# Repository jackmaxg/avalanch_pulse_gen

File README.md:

# avalanch_pulse_gen
Another Incarnation of Jim Williams’ avalanche pulse generator

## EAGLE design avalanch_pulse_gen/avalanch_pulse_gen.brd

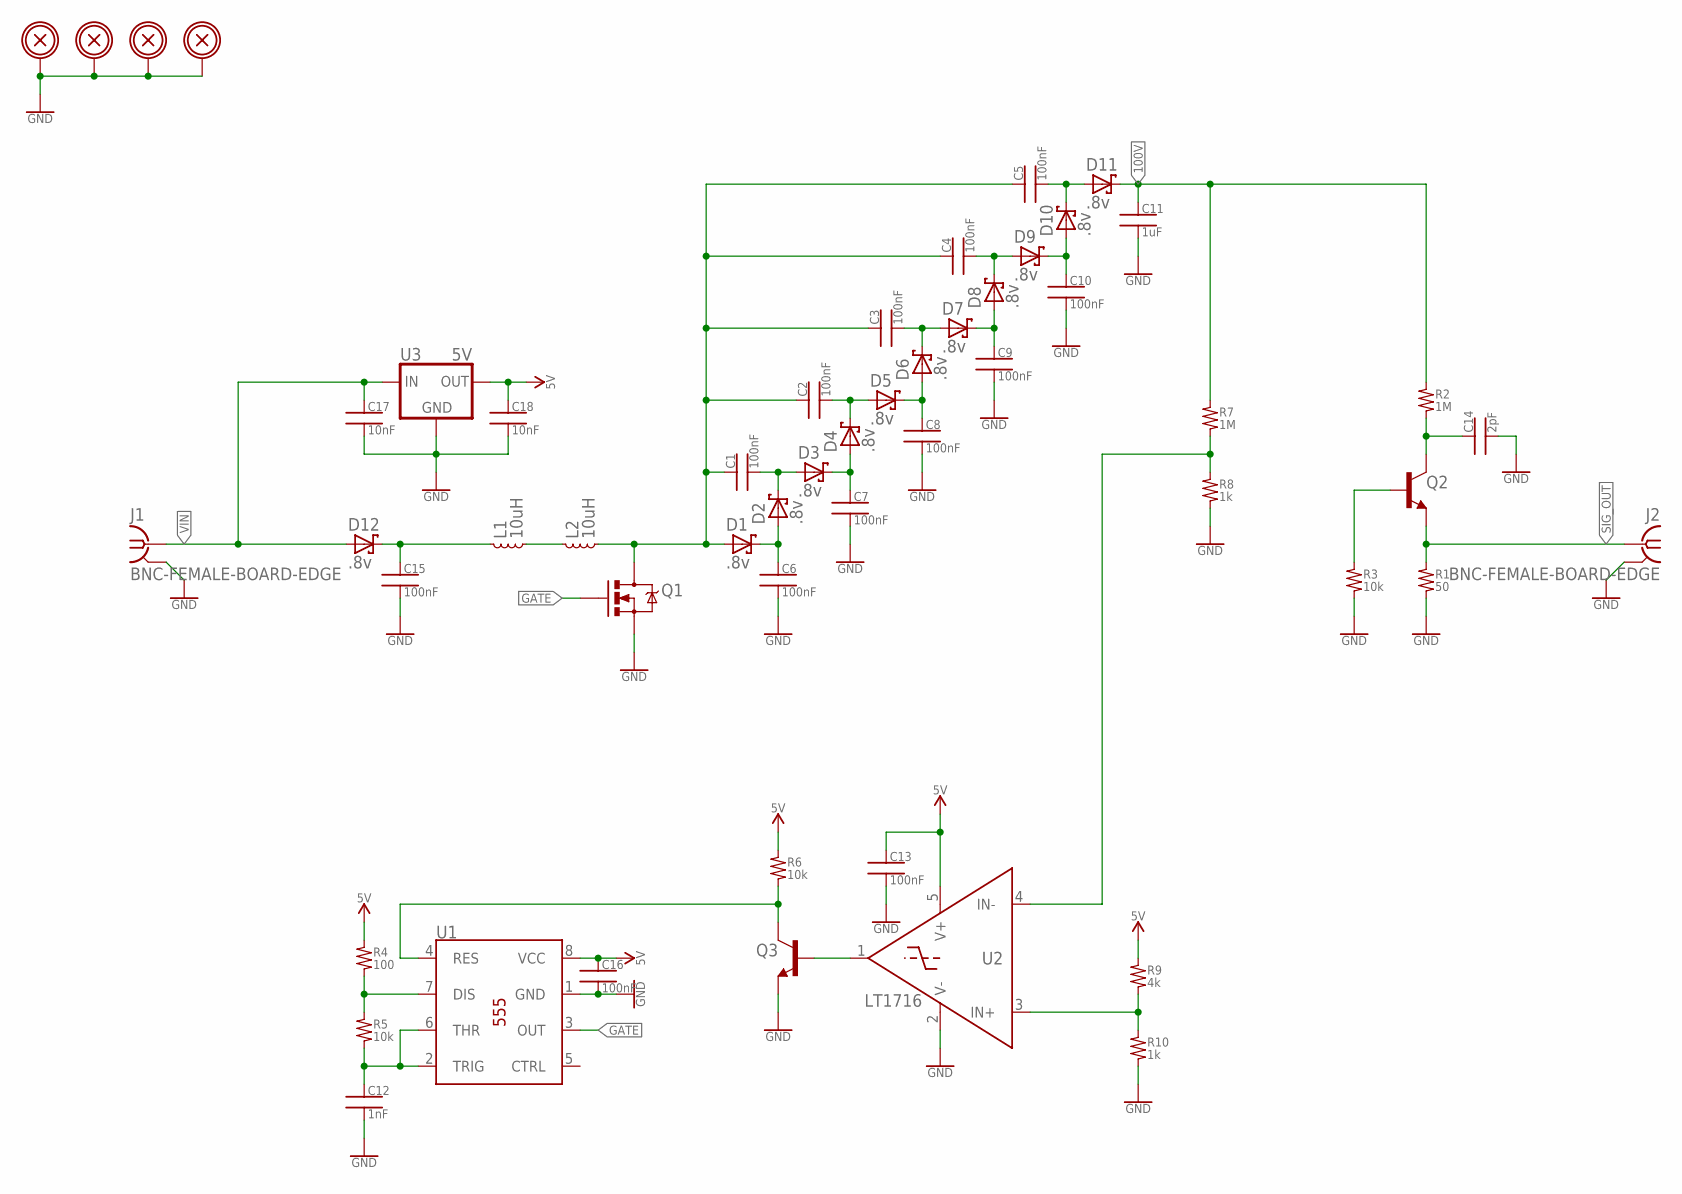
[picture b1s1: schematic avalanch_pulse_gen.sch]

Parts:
C1, C2, C3, C4, C5, C6, C7, C8, C9, C10, C15: 100nF; 1206
C11: 1uF; 2220
C12: 1nF; 0402
C13, C16: 100nF; 0402
C14: 2pF; 0805
C17, C18: 10nF; 0402
D1, D2, D3, D4, D5, D6, D7, D8, D9, D10, D11, D12: .8v; SOD-123
H1, H2, H3, H4: BOLTHOLE_M2.5; M2.5_HOLE
J1, J2: BNC-FEMALE-BOARD-EDGE; AMPHENOL_112640
L1, L2: 10uH; WE74405031100
Q1: MOSFET_N-CHANNEL_SOT23-3; SOT23-3
Q2, Q3: BJT_NPN; SOT23-3
R1: 50; 0402
R2, R7: 1M; 1206
R3, R5, R6: 10k; 0402
R4: 100; 0402
R8, R10: 1k; 0402
R9: 4k; 0402
U1: 555_TIMER_SOIC-8; SOIC_8
U2: LT1716; SOT23-5
U3: 5V; SOT233-4

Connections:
5V: C13.1, C16.1, C18.1, R4.1, R6.1, R9.1, U1.8 (VCC), U2.5 (V+), U3.3 (OUT)
100V: C11.1, D11.1C (C), R2.1, R7.1
GATE: Q1.1 (G), U1.3 (OUT)
GND: C6.2, C7.2, C8.2, C9.2, C10.2, C11.2, C12.2, C13.2, C14.2, C15.2, C16.2, C17.2, C18.2, H1.P, H2.P, H3.P, H4.P, J1.SH1 (GND), J1.SH2 (GND), J1.SH3 (GND), J1.SH4 (GND), J2.SH1 (GND), J2.SH2 (GND), J2.SH3 (GND), J2.SH4 (GND), Q1.2 (S), Q3.2 (E), R1.2, R3.2, R8.2, R10.2, U1.1 (GND), U2.2 (V-), U3.2 (GND), U3.4 (GND)
unnamed: C6.1, D1.1C (C), D2.2A (A)
unnamed: C1.2, D2.1C (C), D3.2A (A)
unnamed: C2.2, D4.1C (C), D5.2A (A)
unnamed: C7.1, D3.1C (C), D4.2A (A)
unnamed: C8.1, D5.1C (C), D6.2A (A)
unnamed: C1.1, C2.1, C3.1, C4.1, C5.1, D1.2A (A), L2.2, Q1.3 (D)
unnamed: C3.2, D6.1C (C), D7.2A (A)
unnamed: C9.1, D7.1C (C), D8.2A (A)
unnamed: C4.2, D8.1C (C), D9.2A (A)
unnamed: C10.1, D9.1C (C), D10.2A (A)
unnamed: C5.2, D10.1C (C), D11.2A (A)
unnamed: C12.1, R5.2, U1.2 (TRIG), U1.6 (THR)
unnamed: Q2.1 (B), R3.1
unnamed: C14.1, Q2.3 (C), R2.2
unnamed: R4.2, R5.1, U1.7 (DIS)
unnamed: Q3.3 (C), R6.2, U1.4 (RES)
unnamed: Q3.1 (B), U2.1 (OUT)
unnamed: R7.2, R8.1, U2.4 (IN-)
unnamed: R9.2, R10.1, U2.3 (IN+)
unnamed: C15.1, D12.1C (C), L1.1
unnamed: L1.2, L2.1
SIG_OUT: J2.SIG (1), Q2.2 (E), R1.1
VIN: C17.1, D12.2A (A), J1.SIG (1), U3.1 (IN)

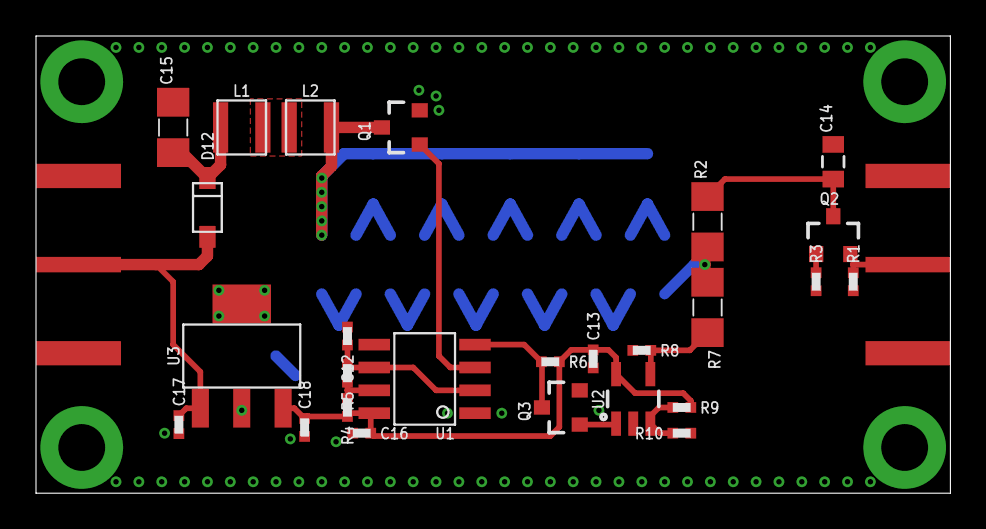
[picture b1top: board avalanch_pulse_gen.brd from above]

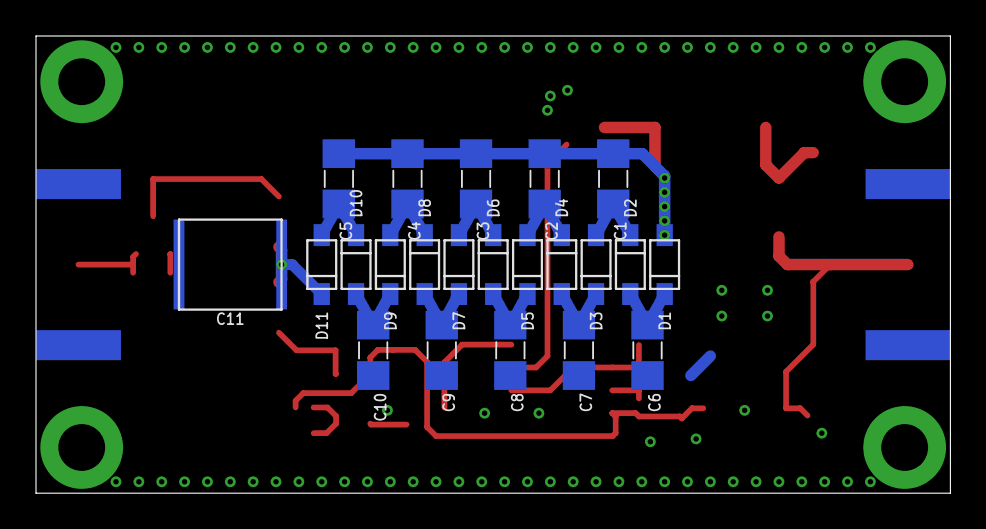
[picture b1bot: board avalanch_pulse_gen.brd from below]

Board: 2 copper layers, 50.8 x 25.4 mm, 54 parts (22 on the bottom side), 27 nets.

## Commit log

2018-08-16 Initial commit of eagle things and also gitignore/gitattributes
2018-08-17 Protyped the power supply circuit
2018-08-28 diddled the simulation bits until everything looked good, made some tweaks to the schematic, and did the board layout. Generated Gerbers to hand off to 3PCB.
